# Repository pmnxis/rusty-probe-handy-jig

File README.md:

# The Rusty Probe

This is an open hardware probe for the Serial Wire Debug (SWD) and JTAG protocol.
Based on the RP2040 MCU.

Following image is forked and modified PCB 3D rendering.
This repo is modified PCB data details are descirbed in [here](#modification-on-this-forked-repo)

## Firmware

The firmware is available [here](https://github.com/probe-rs/rusty-probe-firmware) and is open-source.

## Features

- The 10-pin Cortex-Debug connector is used.
- The programming connector is the Tag Connect TC2030, however for just loading firmware the USB bootloader is recommended.
- Castellated vias for all programming pins, power and 2 GPIOs.
- USB-C connector.
- Target 5V and `Vtarget` is protected with an diode circuit to not have current flow from the target to the host.
- The probe support 1.8v - 3.3v signal voltage and can track `Vtarget`.
- The key pin on the Cortex-Debug can be connected to the protected 5V.

The schematic can be found in the GitHub actions, full production files are generated for each commit.

## Comparison

Here is a small comparison with a few different probes:

|                       | Rusty Probe            | PicoProbe   | Raspberry Pi Debug Probe | STLinkV3           | JLink              |
|-----------------------|------------------------|-------------|--------------------------|--------------------|--------------------|
| Max speed             | 62 MHz                 | ?           | 10 MHz                   | 24 MHz             | 15 MHz             |
| Target support        | any                    | any         | any                      | STM32              | any                |
| IO voltage control    | 1.8-3.3V               | 3.3V        | 3.3V                     | 1.6-3.3V           | 1.6-3.3V somtimes  |
| Type                  | Open Source & Hardware | Open Source | Proprietary              | Proprietary        | Proprietary        |
| Language              | Rust                   | C           | C                        | C                  | C                  |
| Protocol              | CMSIS-DAP              | CMSIS-DAP   | CMSIS-DAP                | Proprietary        | CMSIS-DAP          |
| Programming connector | Cortex-M Debug 10p     | -           | JST                      | Cortex-M Debug 14p | Cortex-M Debug 10p |
| USB speed             | 12 MBit/s              | 12 MBit/s   | 12 MBit/s                | 480 MBit/s         | 12 MBit/s          |

## Where to buy

The original probe is available in the [probe-rs shop](https://shop.probe.rs/). But you are free to build one yourself as well!

## License

This work is licensed under [CERN-OHL-P](cern_ohl_p_v2.txt).

# Modification on this forked repo

The existing rusty-probe has been modified for a practical experiment aiming to enable on-site, real-time firmware updates by individuals without programming knowledge. This modification incorporates BillMock-HW to facilitate firmware updates without the need for a computer.

## PCB Stack-Up
|          |                    |
| -------- | ------------------ |
| Layer    | 4 Layer            |
| Material | FR4                |
| Impedence Control | Don't care (But choosed `JLC04081H-3313` ) |
| Thickness | **0.8 mm**        |

In the modified board, a 1.27mm pin header is positioned at the left end to facilitate connection with a PogoProbe. The board is designed with a thickness of 0.8mm, considering the recommended thickness for the USB-C connector. While the original PCB uses 1.6mm thickness, using the USB-C connector directly (without PogoProbe) allows for the use of 1.6mm thickness as well.

By opting for the 0.8mm thickness, the durability of the PCB might be compromised. To address this, a BackPlane board is employed to reinforce and augment the insufficient rigidity.

| Front   | Back    |
| ------- | ------- |
|  |  |
|  |  |
|  |  |
## Panelization 
JLCPCB's Panelization requires a minimum size of 70mm x 70mm when placing PCBs along the Edge Rail. To meet this requirement, I rotated the PCB by 90 degrees and arranged them in a 4x1 configuration. Additionally, I inserted a dummy bar in the middle for successful Panelization.

### Panlization by cli
```sh
# KiKit Required
cd ./panelize
./panelize_4batch.sh
```

## Changed Note
- Default `W25Q8` is replaced to `IS25WP016D` for custom code.
- Switch `EVQ-P2002W` is replaced to `TS-1145A-C-B` by personal ease of supply and demand of parts.
- Number of tact switch replaced to `TS-1145A-C-B` is changed to **2** from 1. Extra SW2 is connected to GPIO1. The plan of GPIO1 is using for USER input button (Ex Self Programming Button)
- Replace `74LVC1T45` to `X2-DFN1410-6` package and associated part.
- Castellated holes are removed for reducing the small scale unit production cost.
- The addition of a 5x2 SMD pad, designed to accommodate a 1.27mm pin header for vertical connection on the left side, has been made. This pad is intended for connecting a custom Pogo Pin (https://gitlab.com/michael1308/pogoprobe) and currently follows the pinout of the TC-2030 for consideration in the pin mapping of the personal project.
- Optionally added an I2C FRAM on the PCB bottom layer for data logging or frequent data storage purposes.
- Changed the selection of resistors and capacitors to those available in the JLCPCB Basic Part list.
- PCB width is increased to 49.9 mm from 40.0 mm
- Added and modified parameters to enable direct production with JLCPCB.
- Some libraries are referenced from [Lambda_KICAD_LIB](https://github.com/pmnxis/Lambda_KICAD_LIB)
kicad

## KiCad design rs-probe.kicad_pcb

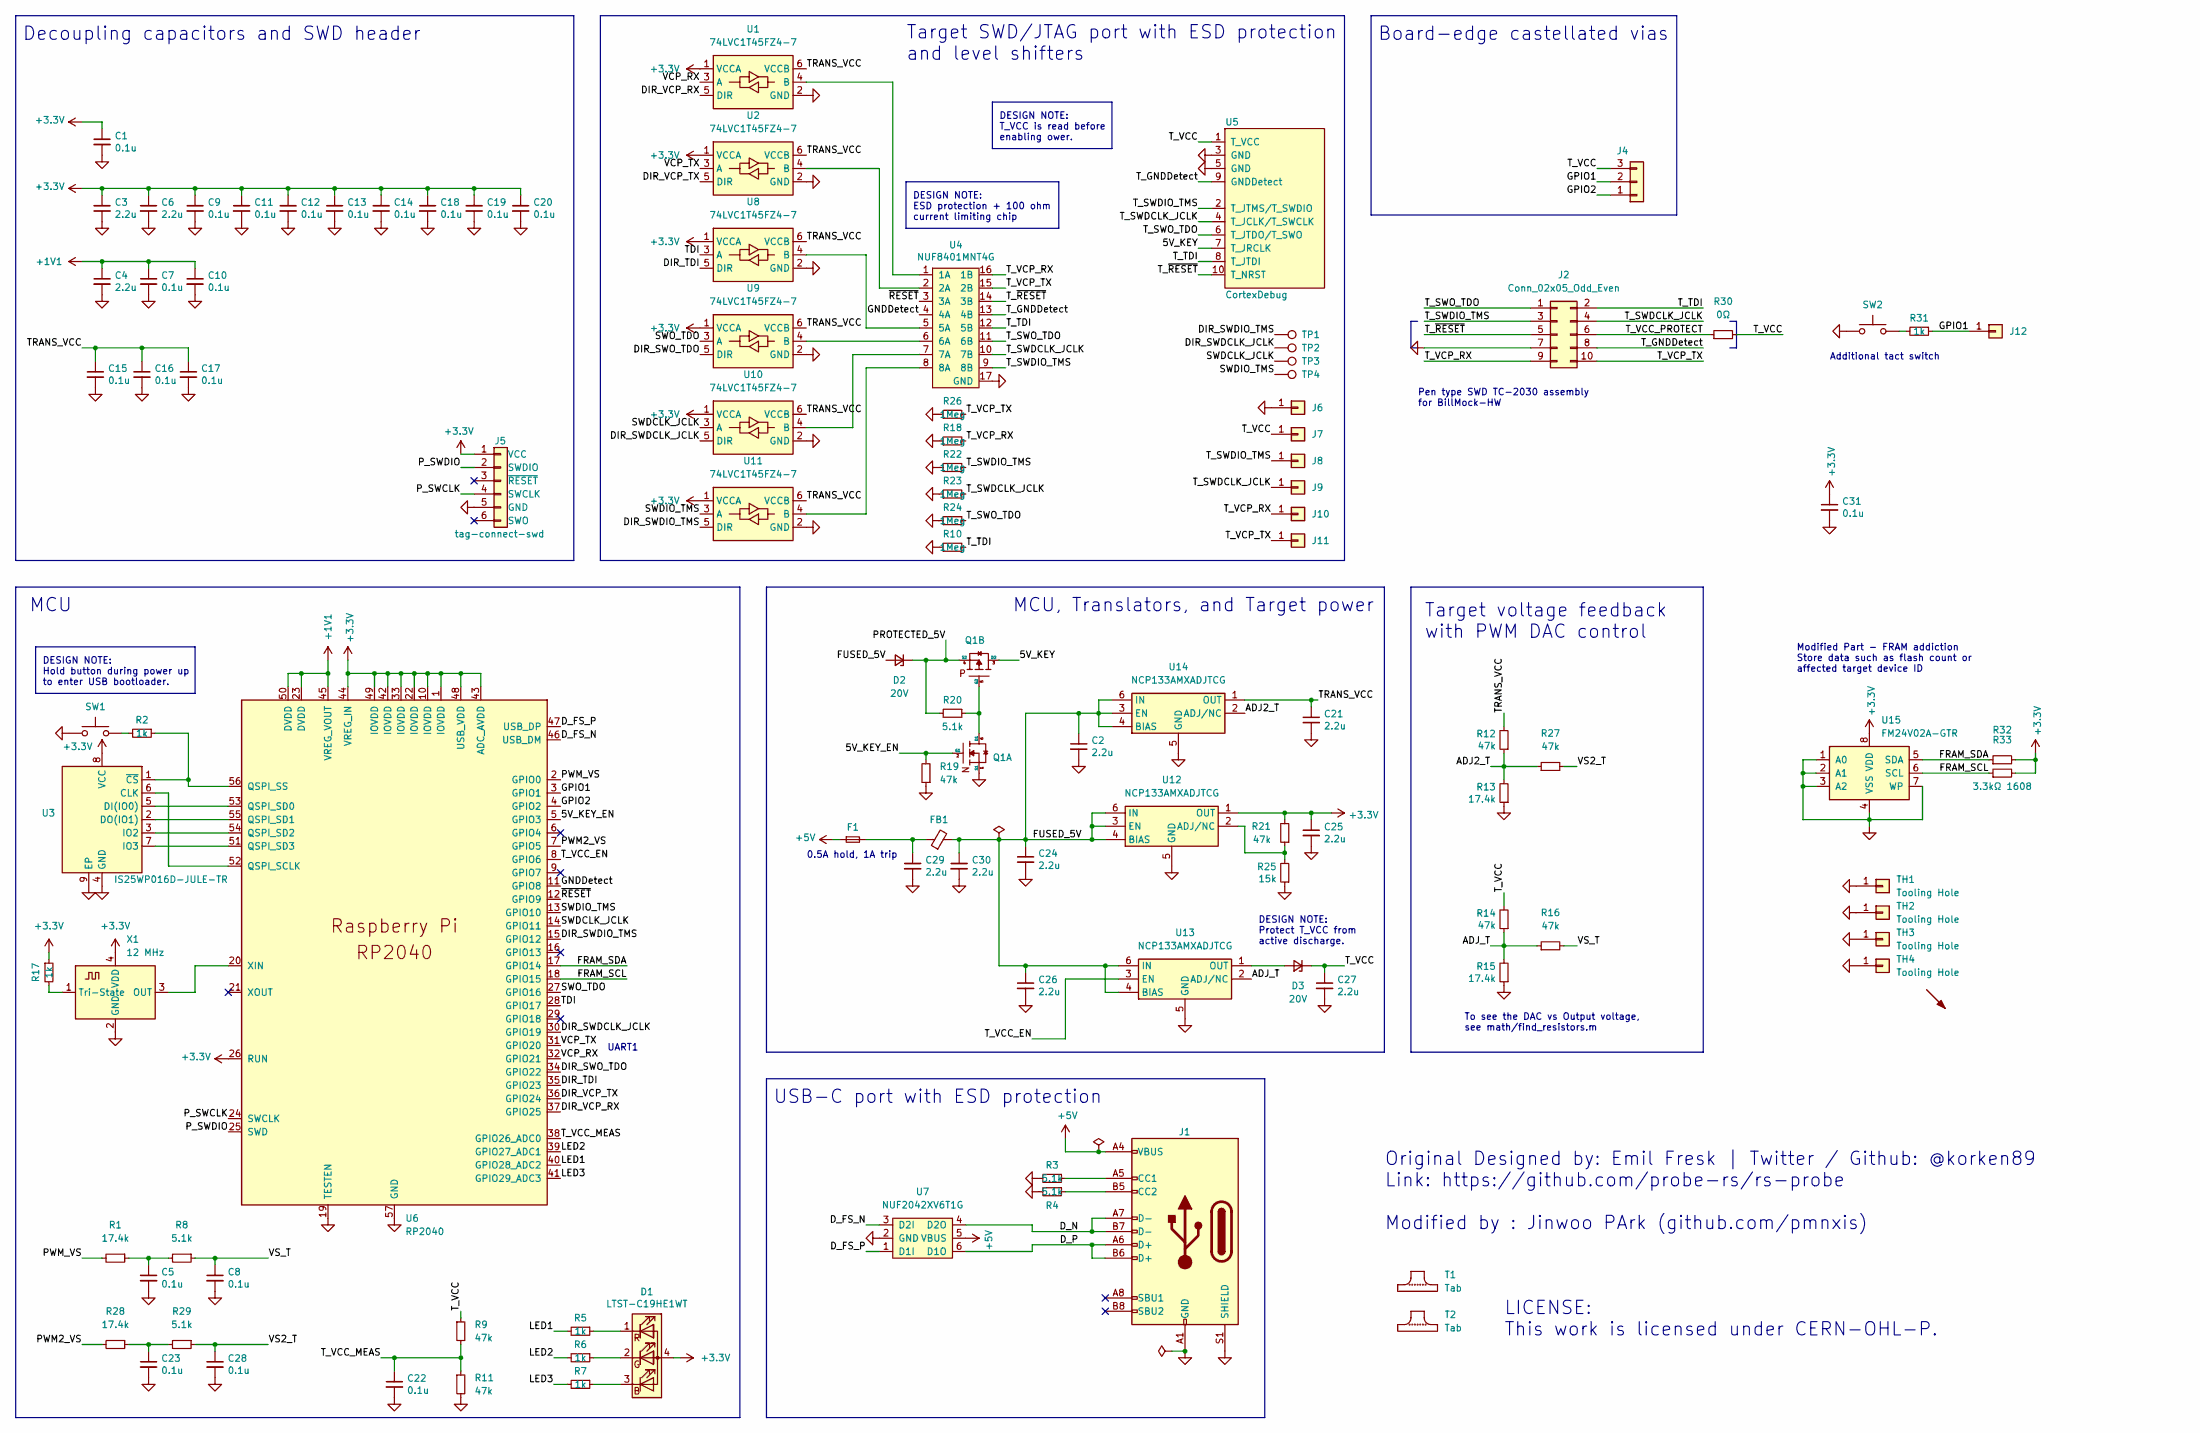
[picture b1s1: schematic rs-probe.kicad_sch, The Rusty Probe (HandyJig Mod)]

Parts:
C1, C5, C7, C8, C9, C10, C11, C12, C13, C14, C15, C16, C17, C18, C19, C20, C22, C23, C28, C31: 0.1u; C_0402; Tolerance 25V, X7R; LCSC C307331
C2, C3, C4, C6, C21, C24, C25, C26, C27, C29, C30: 2.2u; C_0402; Tolerance 10V, X5R; LCSC C170151
D1: LTST-C19HE1WT; LED_LiteOn_LTST-C19HE1WT; LCSC C458749
D2, D3: 20V; D_0402_1005Metric; LCSC C145312
F1: Fuse_Small; Fuse_0603_1608Metric; LCSC C210357
FB1: BLM15AX601SN1D; R_0402; LCSC C76886
J1: USB_C_Receptacle_USB2.0; USB_C_Receptacle_USB4105; LCSC C167321
J2: Conn_02x05_Odd_Even; TC2050-ProbeMod
J4: Castellated Vias; 1x3_1.5mm_castellated
J5: tag-connect-swd; Tag-Connect_TC2030-IDC-NL_2x03_P1.27mm_Vertical
J6, J7, J8, J9, J10, J11, J12: Conn_01x01; pad_1.5x2.0mm
Q1: NTZD3155C; SOT-563; LCSC C895156
R1, R13, R15, R28: 17.4k; R_0402; Tolerance 1%; LCSC C26957
R2, R5, R6, R7, R17, R31: 1k; R_0402; Tolerance 1%; LCSC C11702
R3, R4, R8, R20, R29: 5.1k; R_0402; Tolerance 1%; LCSC C25905
R9, R11, R12, R14, R16, R19, R21, R27: 47k; R_0402; Tolerance 1%; LCSC C25792
R10, R18, R22, R23, R24, R26: 1Meg; R_0402; Tolerance 1%; LCSC C138033
R25: 15k; R_0402; Tolerance 1%; LCSC C25756
R30: 0Ω; R_0402; Tolerance 1%; LCSC C17168
R32, R33: 3.3kΩ 1608; R_0603; Tolerance 1%; LCSC C22978
SW1, SW2: TS-1145A-C-B; SW_SPST_TS-1145A; LCSC C465998
SYM1: SYM_Arrow45_Normal; LamudaEE-12.3x7.6mm
T1, T2: Tab
TH1, TH2, TH3, TH4: Tooling Hole
TP1, TP2, TP3, TP4: TestPoint; TestPoint_Pad_D1.0mm
U1, U2, U8, U9, U10, U11: 74LVC1T45FZ4-7; X2-DFN1410-6; LCSC C150482
U3: IS25WP016D-JULE-TR; USON-8-3x2mm-EP; LCSC C2976734
U4: NUF8401MNT4G; DFN-16-1EP_1.6x4mm_P0.5mm; LCSC C895158
U5: CortexDebug; PinHeader_2x05_FTSH-105-01-L-DV-K; LCSC C448647
U6: RP2040; RP2040-QFN-56; LCSC C2040
U7: NUF2042XV6T1G; SOT-563; LCSC C90707
U12, U13, U14: NCP133AMXADJTCG; DFN-6-1EP_1.2x1.2mm_P0.4mm_EP0.3x0.94mm_PullBack; LCSC C457672
U15: FM24V02A-GTR; SOIC-8_3.9x4.9mm_P1.27mm; LCSC C382041
X1: 12 MHz; Crystal_SMD_2520-4Pin_2.5x2.0mm; LCSC C255991

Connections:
+1V1: C4.1, C7.1, C10.1, U6.23 (DVDD), U6.45 (VREG_VOUT), U6.50 (DVDD)
+3.3V: C1.1, C3.1, C6.1, C9.1, C11.1, C12.1, C13.1, C14.1, C18.1, C19.1, C20.1, C25.1, C31.1, D1.4 (A), J5.1 (VCC), R17.1, R21.2, R32.2, R33.2, U1.1 (VCCA), U2.1 (VCCA), U3.8 (VCC), U6.1 (IOVDD), U6.10 (IOVDD), U6.22 (IOVDD), U6.26 (RUN), U6.33 (IOVDD), U6.42 (IOVDD), U6.43 (ADC_AVDD), U6.44 (VREG_IN), U6.48 (USB_VDD), U6.49 (IOVDD), U8.1 (VCCA), U9.1 (VCCA), U10.1 (VCCA), U11.1 (VCCA), U12.1 (OUT), U15.8 (VDD), X1.4 (VDD)
+5V: F1.1, J1.A4 (VBUS), J1.A9 (VBUS), J1.B4 (VBUS), J1.B9 (VBUS), U7.5 (VBUS)
/5V_KEY: Q1.3 (D2), U5.7 (T_JRCLK)
/5V_KEY_EN: Q1.2 (G1), R19.2, U6.5 (GPIO3)
/ADJ2_T: R12.1, R13.2, R27.1, U14.2 (ADJ/NC)
/ADJ_T: R14.1, R15.2, R16.1, U13.2 (ADJ/NC)
/DIR_SWDCLK_JCLK: TP2.1, U6.30 (GPIO19), U10.5 (DIR)
/DIR_SWDIO_TMS: TP1.1, U6.15 (GPIO12), U11.5 (DIR)
/DIR_SWO_TDO: U6.34 (GPIO22), U9.5 (DIR)
/DIR_TDI: U6.35 (GPIO23), U8.5 (DIR)
/DIR_VCP_RX: U1.5 (DIR), U6.37 (GPIO25)
/DIR_VCP_TX: U2.5 (DIR), U6.36 (GPIO24)
/D_FS_N: U6.46 (USB_DM), U7.3 (D2I)
/D_FS_P: U6.47 (USB_DP), U7.1 (D1I)
/D_N: J1.A7 (D-), J1.B7 (D-), U7.4 (D2O)
/D_P: J1.A6 (D+), J1.B6 (D+), U7.6 (D1O)
/FRAM_SCL: R33.1, U6.18 (GPIO15), U15.6 (SCL)
/FRAM_SDA: R32.1, U6.17 (GPIO14), U15.5 (SDA)
/FUSED_5V: C2.1, C24.1, C26.1, C30.1, D2.2 (A), FB1.2, U12.3 (EN), U12.4 (BIAS), U12.6 (IN), U13.4 (BIAS), U13.6 (IN), U14.3 (EN), U14.4 (BIAS), U14.6 (IN)
/GNDDetect: U4.4 (4A), U6.11 (GPIO8)
/GPIO1: J4.2, J12.1, R31.1, U6.3 (GPIO1)
/GPIO2: J4.1, U6.4 (GPIO2)
/LED1: R5.2, U6.40 (GPIO28_ADC2)
/LED2: R6.2, U6.39 (GPIO27_ADC1)
/LED3: R7.2, U6.41 (GPIO29_ADC3)
/PROTECTED_5V: D2.1 (K), Q1.4 (S2), R20.2
/PWM2_VS: R28.2, U6.7 (GPIO5)
/PWM_VS: R1.2, U6.2 (GPIO0)
/P_SWCLK: J5.4 (SWCLK), U6.24 (SWCLK)
/P_SWDIO: J5.2 (SWDIO), U6.25 (SWD)
/SWDCLK_JCLK: TP3.1, U6.14 (GPIO11), U10.3 (A)
/SWDIO_TMS: TP4.1, U6.13 (GPIO10), U11.3 (A)
/SWO_TDO: U6.27 (GPIO16), U9.3 (A)
/TDI: U6.28 (GPIO17), U8.3 (A)
/TRANS_VCC: C15.1, C16.1, C17.1, C21.1, R12.2, U1.6 (VCCB), U2.6 (VCCB), U8.6 (VCCB), U9.6 (VCCB), U10.6 (VCCB), U11.6 (VCCB), U14.1 (OUT)
/T_GNDDetect: J2.8, U4.13 (4B), U5.9 (GNDDetect)
/T_SWDCLK_JCLK: J2.4, J9.1, R23.2, U4.10 (7B), U5.4 (T_JCLK/T_SWCLK)
/T_SWDIO_TMS: J2.3, J8.1, R22.2, U4.9 (8B), U5.2 (T_JTMS/T_SWDIO)
/T_SWO_TDO: J2.1, R24.2, U4.11 (6B), U5.6 (T_JTDO/T_SWO)
/T_TDI: J2.2, R10.2, U4.12 (5B), U5.8 (T_JTDI)
/T_VCC: C27.1, D3.1 (K), J4.3, J7.1, R9.1, R14.2, R30.2, U5.1 (T_VCC)
/T_VCC_EN: U6.8 (GPIO6), U13.3 (EN)
/T_VCC_MEAS: C22.1, R9.2, R11.1, U6.38 (GPIO26_ADC0)
/T_VCC_PROTECT: J2.6, R30.1
/T_VCP_RX: J2.9, J10.1, R18.2, U4.16 (1B)
/T_VCP_TX: J2.10, J11.1, R26.2, U4.15 (2B)
/T_~RESET: J2.5, U4.14 (3B), U5.10 (T_NRST)
/VCP_RX: U1.3 (A), U6.32 (GPIO21)
/VCP_TX: U2.3 (A), U6.31 (GPIO20)
/VS2_T: C28.1, R27.2, R29.1
/VS_T: C8.1, R8.1, R16.2
/~RESET: U4.3 (3A), U6.12 (GPIO9)
GND: C1.2, C2.2, C3.2, C4.2, C5.2, C6.2, C7.2, C8.2, C9.2, C10.2, C11.2, C12.2, C13.2, C14.2, C15.2, C16.2, C17.2, C18.2, C19.2, C20.2, C21.2, C22.2, C23.2, C24.2, C25.2, C26.2, C27.2, C28.2, C29.2, C30.2, C31.2, J1.A1 (GND), J1.A12 (GND), J1.B1 (GND), J1.B12 (GND), J1.S1 (SHIELD), J2.7, J5.5 (GND), J6.1, Q1.1 (S1), R3.2, R4.2, R10.1, R11.2, R13.1, R15.1, R18.1, R19.1, R22.1, R23.1, R24.1, R25.1, R26.1, SW1.1, SW2.1, TH1.1, TH2.1, TH3.1, TH4.1, U1.2 (GND), U2.2 (GND), U3.4 (GND), U3.9 (EP), U4.17 (GND), U5.3 (GND), U5.5 (GND), U6.19 (TESTEN), U6.57 (GND), U7.2 (GND), U8.2 (GND), U9.2 (GND), U10.2 (GND), U11.2 (GND), U12.5 (GND), U12.7 (GND), U13.5 (GND), U13.7 (GND), U14.5 (GND), U14.7 (GND), U15.1 (A0), U15.2 (A1), U15.3 (A2), U15.4 (VSS), U15.7 (WP), X1.2 (GND)
unnamed: C5.1, R1.1, R8.2
unnamed: C23.1, R28.1, R29.2
unnamed: C29.1, F1.2, FB1.1
unnamed: D1.3 (BK), R7.1
unnamed: D1.2 (GK), R6.1
unnamed: D1.1 (RK), R5.1
unnamed: D3.2 (A), U13.1 (OUT)
unnamed: J1.A5 (CC1), R3.1
unnamed: J1.B5 (CC2), R4.1
unnamed: Q1.5 (G2), Q1.6 (D1), R20.1
unnamed: R2.2, SW1.2
unnamed: R31.2, SW2.2
unnamed: U1.4 (B), U4.1 (1A)
unnamed: U2.4 (B), U4.2 (2A)
unnamed: U3.6 (CLK), U6.52 (QSPI_SCLK)
unnamed: U3.5 (DI(IO0)), U6.53 (QSPI_SD0)
unnamed: U3.2 (DO(IO1)), U6.55 (QSPI_SD1)
unnamed: U3.3 (IO2), U6.54 (QSPI_SD2)
unnamed: U3.7 (IO3), U6.51 (QSPI_SD3)
unnamed: R2.1, U3.1 (~CS), U6.56 (QSPI_SS)
unnamed: U4.5 (5A), U8.4 (B)
unnamed: U4.6 (6A), U9.4 (B)
unnamed: U6.20 (XIN), X1.3 (OUT)
unnamed: U4.7 (7A), U10.4 (B)
unnamed: U4.8 (8A), U11.4 (B)
unnamed: R21.1, R25.2, U12.2 (ADJ/NC)
unnamed: R17.2, X1.1 (Tri-State)

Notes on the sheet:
Target SWD/JTAG port with ESD protection and level shifters
Target voltage feedback with PWM DAC control
To see the DAC vs Output voltage, see math/find_resistors.m
USB-C port with ESD protection
DESIGN NOTE: T_VCC is read before enabling ower.
Original Designed by: Emil Fresk | Twitter / Github: @korken89 Link: https://github.com/probe-rs/rs-probe Modified by : Jinwoo PArk (github.com/pmnxis)
Modified Part - FRAM addiction Store data such as flash count or affected target device ID
Board-edge castellated vias
DESIGN NOTE: ESD protection + 100 ohm current limiting chip
Pen type SWD TC-2030 assembly for BillMock-HW
Decoupling capacitors and SWD header
MCU
0.5A hold, 1A trip
MCU, Translators, and Target power
DESIGN NOTE: Protect T_VCC from active discharge.
Additional tact switch
DESIGN NOTE: Hold button during power up to enter USB bootloader.
UART1
LICENSE: This work is licensed under CERN-OHL-P.

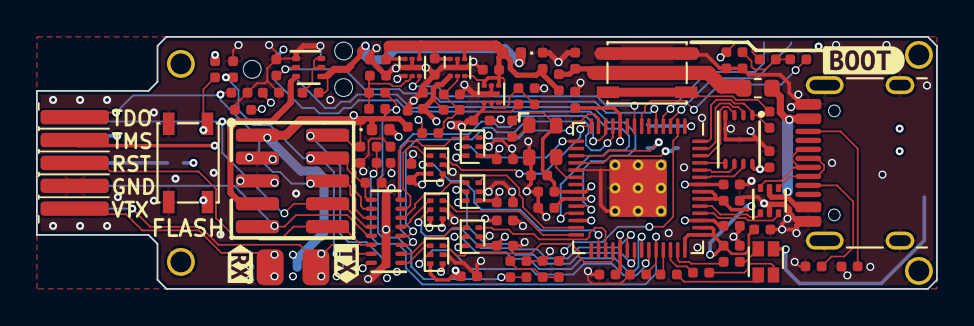
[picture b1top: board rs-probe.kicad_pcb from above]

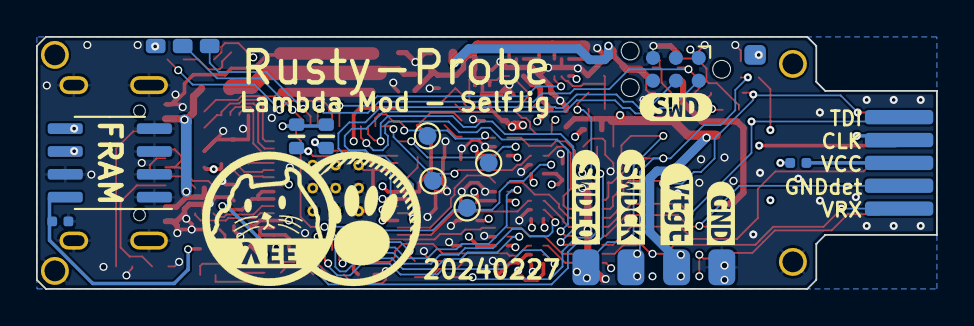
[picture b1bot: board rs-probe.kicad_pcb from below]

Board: 4 copper layers, 50.0 x 14.0 mm, 120 parts (22 on the bottom side), 81 nets.

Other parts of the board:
T1#2, T2#2: Tab
kibuzzard-61EE8014: G***; kibuzzard-61EE8014
kibuzzard-61FE7ECB: G***; kibuzzard-61FE7ECB
kibuzzard-61FE80B0: G***; kibuzzard-61FE80B0
kibuzzard-61FE80BD: G***; kibuzzard-61FE80BD
kibuzzard-61FE8065: G***; kibuzzard-61FE8065
kibuzzard-61FE8092: G***; kibuzzard-61FE8092
kibuzzard-6228D4B3: G***; kibuzzard-6228D4B3
kibuzzard-6228D4CF: G***; kibuzzard-6228D4CF

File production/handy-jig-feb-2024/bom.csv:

Designator,Footprint,Quantity,Value,LCSC Part #
"C1, C10, C11, C12, C13, C14, C15, C16, C17, C18, C19, C20, C22, C23, C28, C31, C5, C7, C8, C9",C_0402,20,0.1u,C307331
"C2, C21, C24, C25, C26, C27, C29, C3, C30, C4, C6",C_0402,11,2.2u,C170151
D1,LED_LiteOn_LTST-C19HE1WT,1,LTST-C19HE1WT,C458749
"D2, D3",0402,2,20V,C145312
F1,0603,1,Fuse_Small,C210357
FB1,R_0402,1,BLM15AX601SN1D,C76886
J1,USB_C_Receptacle_USB4105,1,USB_C_Receptacle_USB2.0,C167321
Q1,SOT-563,1,NTZD3155C,C895156
"R1, R13, R15, R28",R_0402,4,17.4k,C26957
"R10, R18, R22, R23, R24, R26",R_0402,6,1Meg,C138033
"R11, R12, R14, R16, R19, R21, R27, R9",R_0402,8,47k,C25792
"R17, R2, R31, R5, R6, R7",R_0402,6,1k,C11702
"R20, R29, R3, R4, R8",R_0402,5,5.1k,C25905
R25,R_0402,1,15k,C25756
R30,R_0402,1,0Ω,C17168
"R32, R33",R_0603,2,3.3kΩ 1608,C22978
"SW1, SW2",SW_SPST_TS-1145A,2,TS-1145A-C-B,C465998
"U1, U10, U11, U2, U8, U9",X2-DFN1410-6,6,74LVC1T45FZ4-7,C150482
"U12, U13, U14",DFN-6-1EP_1.2x1.2mm_P0.4mm_EP0.3x0.94mm_PullBack,3,NCP133AMXADJTCG,C457672
U15,SOIC-8_3.9x4.9mm_P1.27mm,1,FM24V02A-GTR,C382041
U3,USON-8-3x2mm-EP,1,IS25WP016D-JULE-TR,C2976734
U4,DFN-16-1EP_1.6x4mm_P0.5mm,1,NUF8401MNT4G,C895158
U5,PinHeader_2x05_FTSH-105-01-L-DV-K,1,CortexDebug,C448647
U6,RP2040-QFN-56,1,RP2040,C2040
U7,SOT-563,1,NUF2042XV6T1G,C90707
X1,Crystal_SMD_2520-4Pin_2.5x2.0mm,1,12 MHz,C255991

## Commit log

2024-02-09 Modification for BillMock-HW on-site programming
2024-03-01 Fabricated on JLCPCB (not tested yet)
2024-03-01 Add assembly image
2024-04-08 final production file
